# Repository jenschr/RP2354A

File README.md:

# RP2354A
Kicad design for a minimal RP2354A based devboard, based on the original files from Raspberry Pi. Made in a small form factor, 2-layer board that can be produced anywhere. I'll update the repo with more images once I've made some copies myself.

Feel free to use this as a starting point for your own projects. [Contact me](https://maketronics.no/about/) for consulting and custom hardware based around RP2354A or other hardware.

Raspberry Pi MPN used for test board: SC1511(13)-A4.

## Versions
- v1.1 Swapped the TCR8BM33A for a more easily available and cheaper AP2112K-3.3. Takes more space, but just works. The extra space allowed one more pin on each side, so VIN/USB and IO12 is now broken out.
- v1.0 used the Toshiba LDO TCR8BM33A. This is just to fiddly for DIY boards and due to poor datasheet, I got the bias wrong.

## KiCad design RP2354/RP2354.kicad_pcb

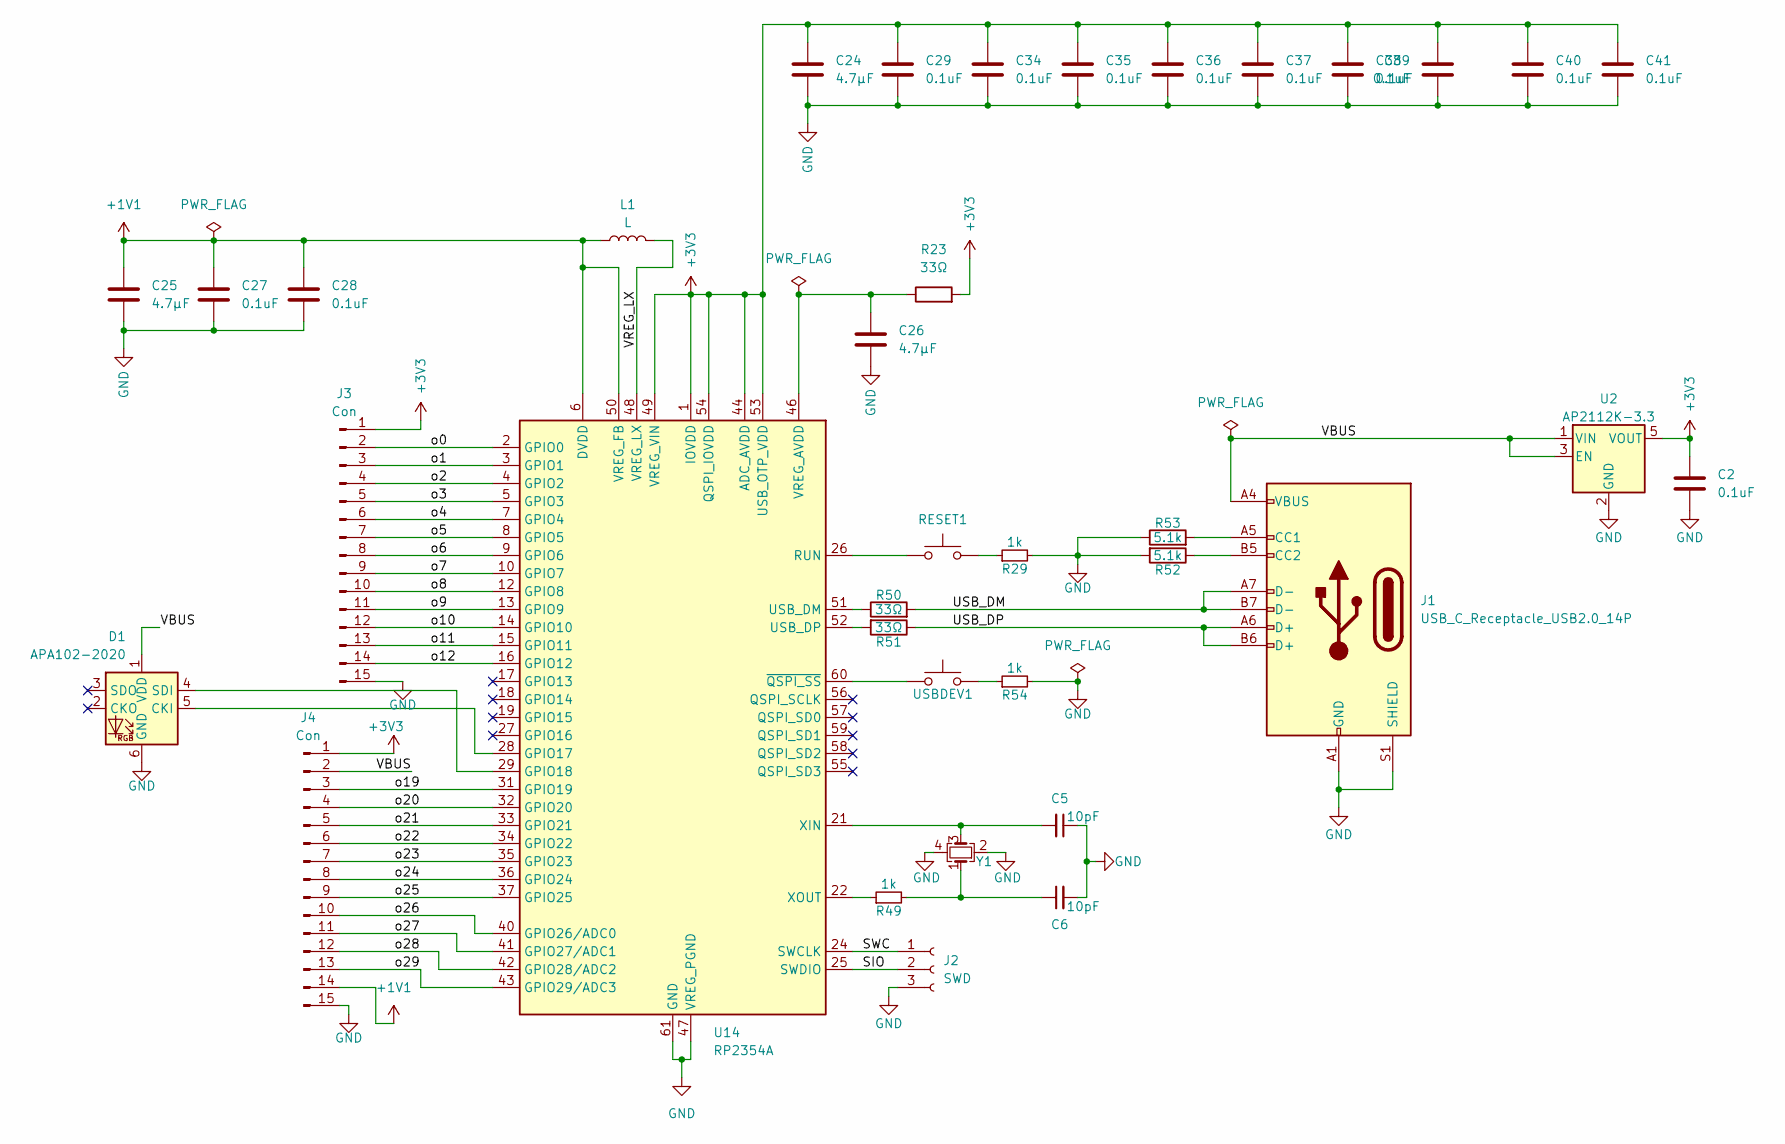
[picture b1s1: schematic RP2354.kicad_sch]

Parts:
C2, C27, C28, C29, C34, C35, C36, C37, C38, C39, C40, C41: 0.1uF; C_0402_1005Metric; MPN CL05B104KA5NNNC
C5, C6: 10pF; C_0603_1608Metric; MPN CL10C100JB8NFNC
C24, C25, C26: 4.7μF; C_0402_1005Metric; MPN GRM155D80E475ME47J
D1: APA102-2020; LED-APA102-2020; MPN 3341
J1: USB_C_Receptacle_USB2.0_14P; TYPE-C-31-M-14; MPN TYPE-C-31-M-14
J2: SWD; PinHeader_1x03_P2.54mm_Vertical
J3, J4: Con; PinHeader_1x15_P2.54mm_Vertical
L1: L; R_0805_2012Metric; MPN AOTA-B201610S3R3-101-T
R23, R50, R51: 33Ω; R_0402_1005Metric; MPN RC0402FR-0733RL
R29, R49, R54: 1k; R_0603_1608Metric; MPN RT0603FRE101KL
R52, R53: 5.1k; R_0402_1005Metric; MPN RC0402FR-075K1L
RESET1: SW_Push; SW_Push_1P1T_NO_CK_KMR2; MPN KMR241G LFS
U2: AP2112K-3.3; SOT-23-5; MPN AP2112K-3.3TRG1
U14: RP2354A; QFN-60-1EP_7x7mm_P0.4mm_EP3.4x3.4mm; MPN SC1511(13)-A4
USBDEV1: SW_Push; SW_Push_1P1T_NO_CK_KMR2; MPN KMR241G LFS
Y1: Crystal; Crystal_SMD_3225-4Pin_3.2x2.5mm; MPN ABM8-272-T3

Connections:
+1V1: C25.1, C27.2, C28.2, J4.14, L1.1, U14.6 (DVDD), U14.23 (DVDD), U14.39 (DVDD), U14.50 (VREG_FB)
+3V3: C2.2, C24.1, C29.2, C34.2, C35.2, C36.2, C37.2, C38.2, C39.2, C40.2, C41.2, J3.1, J4.1, R23.2, U2.5 (VOUT), U14.1 (IOVDD), U14.11 (IOVDD), U14.20 (IOVDD), U14.30 (IOVDD), U14.38 (IOVDD), U14.44 (ADC_AVDD), U14.45 (IOVDD), U14.49 (VREG_VIN), U14.53 (USB_OTP_VDD), U14.54 (QSPI_IOVDD)
/SIO: J2.2, U14.25 (SWDIO)
/SWC: J2.1, U14.24 (SWCLK)
/USB_DM: J1.A7 (D-), J1.B7 (D-), R50.2
/USB_DP: J1.A6 (D+), J1.B6 (D+), R51.1
/VBUS: D1.1 (VDD), J1.A4 (VBUS), J1.A9 (VBUS), J1.B4 (VBUS), J1.B9 (VBUS), J4.2, U2.1 (VIN), U2.3 (EN)
/VREG_LX: L1.2, U14.48 (VREG_LX)
/o0: J3.2, U14.2 (GPIO0)
/o1: J3.3, U14.3 (GPIO1)
/o2: J3.4, U14.4 (GPIO2)
/o3: J3.5, U14.5 (GPIO3)
/o4: J3.6, U14.7 (GPIO4)
/o5: J3.7, U14.8 (GPIO5)
/o6: J3.8, U14.9 (GPIO6)
/o7: J3.9, U14.10 (GPIO7)
/o8: J3.10, U14.12 (GPIO8)
/o9: J3.11, U14.13 (GPIO9)
/o10: J3.12, U14.14 (GPIO10)
/o11: J3.13, U14.15 (GPIO11)
/o12: J3.14, U14.16 (GPIO12)
/o19: J4.3, U14.31 (GPIO19)
/o20: J4.4, U14.32 (GPIO20)
/o21: J4.5, U14.33 (GPIO21)
/o22: J4.6, U14.34 (GPIO22)
/o23: J4.7, U14.35 (GPIO23)
/o24: J4.8, U14.36 (GPIO24)
/o25: J4.9, U14.37 (GPIO25)
/o26: J4.10, U14.40 (GPIO26/ADC0)
/o27: J4.11, U14.41 (GPIO27/ADC1)
/o28: J4.12, U14.42 (GPIO28/ADC2)
/o29: J4.13, U14.43 (GPIO29/ADC3)
GND: C2.1, C5.1, C6.2, C24.2, C25.2, C26.2, C27.1, C28.1, C29.1, C34.1, C35.1, C36.1, C37.1, C38.1, C39.1, C40.1, C41.1, D1.6 (GND), J1.A1 (GND), J1.A12 (GND), J1.B1 (GND), J1.B12 (GND), J1.S1 (SHIELD), J2.3, J3.15, J4.15, R29.2, R52.2, R53.1, R54.2, U2.2 (GND), U14.47 (VREG_PGND), U14.61 (GND), Y1.2, Y1.4
unnamed: C6.1, R49.2, Y1.1
unnamed: D1.5 (CKI), U14.28 (GPIO17)
unnamed: D1.4 (SDI), U14.29 (GPIO18)
unnamed: J1.A5 (CC1), R53.2
unnamed: J1.B5 (CC2), R52.1
unnamed: R29.1, RESET1.2
unnamed: R54.1, USBDEV1.2
unnamed: RESET1.1, U14.26 (RUN)
unnamed: R50.1, U14.51 (USB_DM)
unnamed: R51.2, U14.52 (USB_DP)
unnamed: C26.1, R23.1, U14.46 (VREG_AVDD)
unnamed: C5.2, U14.21 (XIN), Y1.3
unnamed: R49.1, U14.22 (XOUT)
unnamed: U14.60 (~QSPI_SS), USBDEV1.1

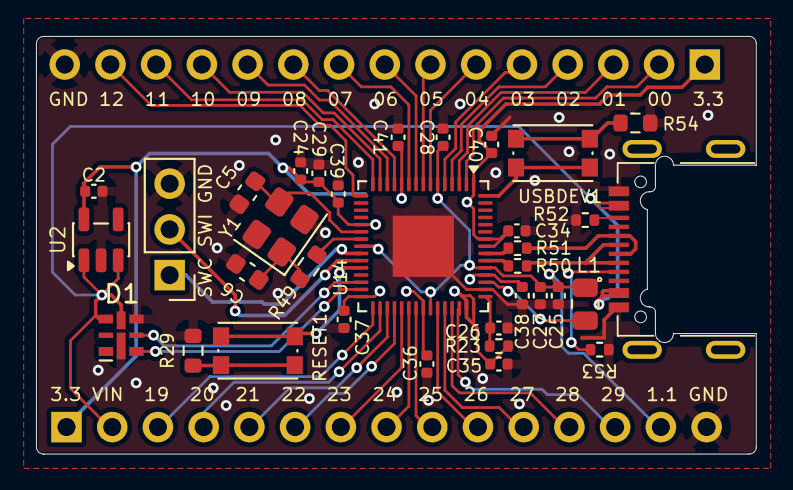
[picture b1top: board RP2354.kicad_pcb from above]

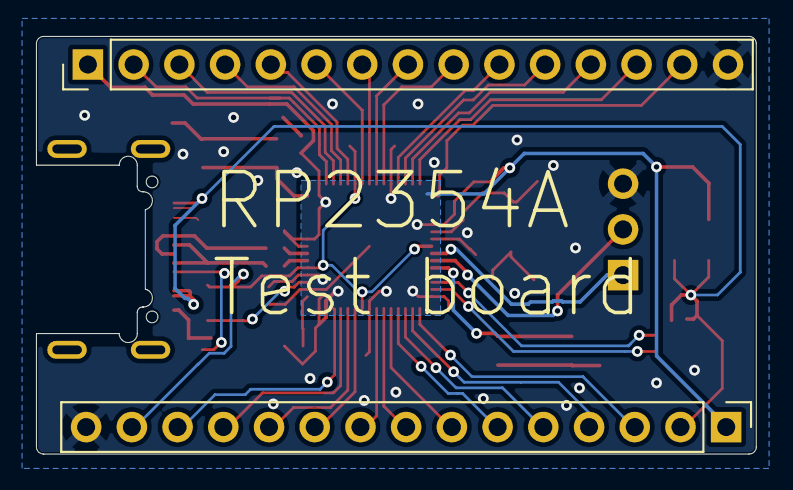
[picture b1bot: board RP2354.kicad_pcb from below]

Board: 2 copper layers, 40.0 x 23.2 mm, 36 parts (2 on the bottom side), 47 nets.

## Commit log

2026-02-19 v1.0 files as sent to JLC
2026-02-19 Quick pass at ERC
2026-02-19 MPN's added for most parts. iBom export
2026-03-01 Updated with a larger 3.3V regulator. The added pins break out +5V/USB and IO12 as well. The TCR8BM is just too fiddly for DIY boards and the datasheet isn't good enough.
2026-03-01 Layout tweak. Doc update.
2026-03-01 Swapped for larger inductor footprint on L1. 0805 resistor is correct.
